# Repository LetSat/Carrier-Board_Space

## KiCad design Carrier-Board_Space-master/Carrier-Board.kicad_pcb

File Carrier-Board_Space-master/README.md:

# Carrier-Board_Space
mCom-TK1 carrier board. This is the actual board for space.

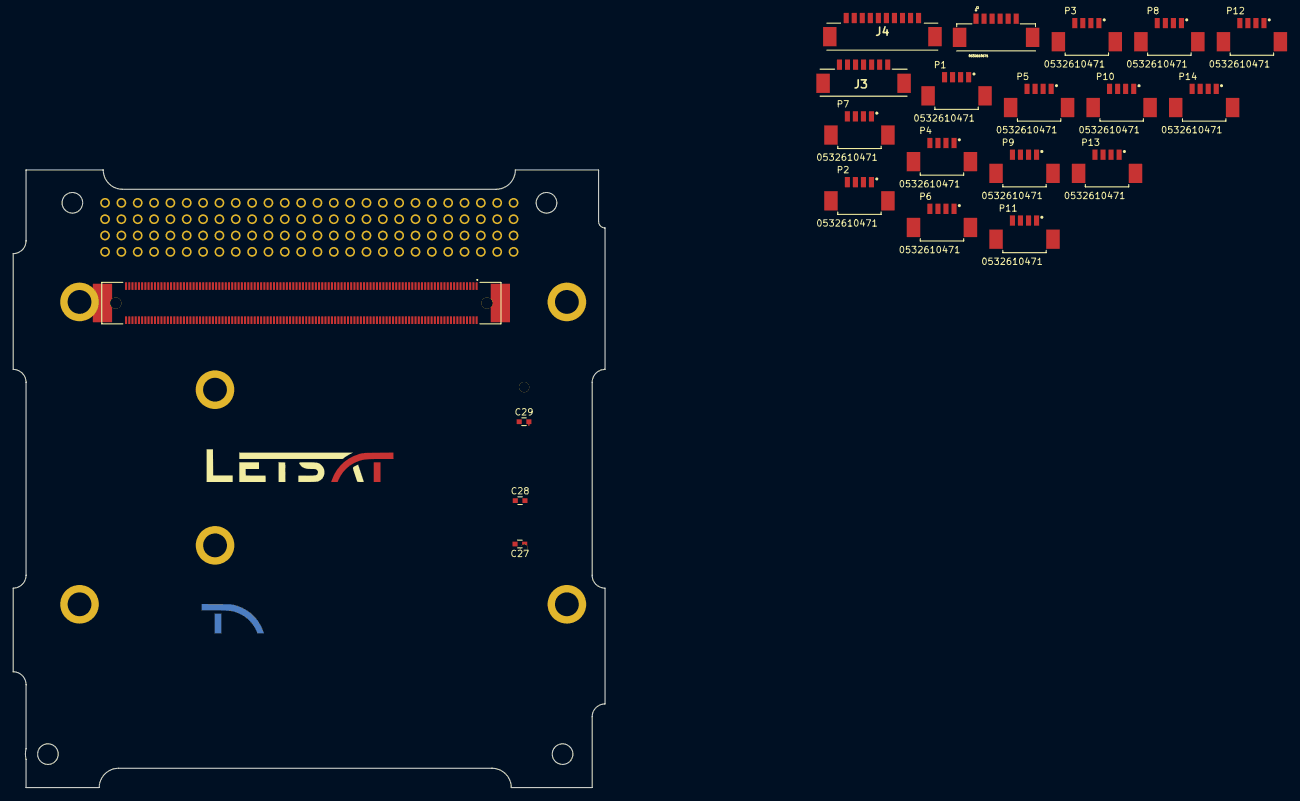
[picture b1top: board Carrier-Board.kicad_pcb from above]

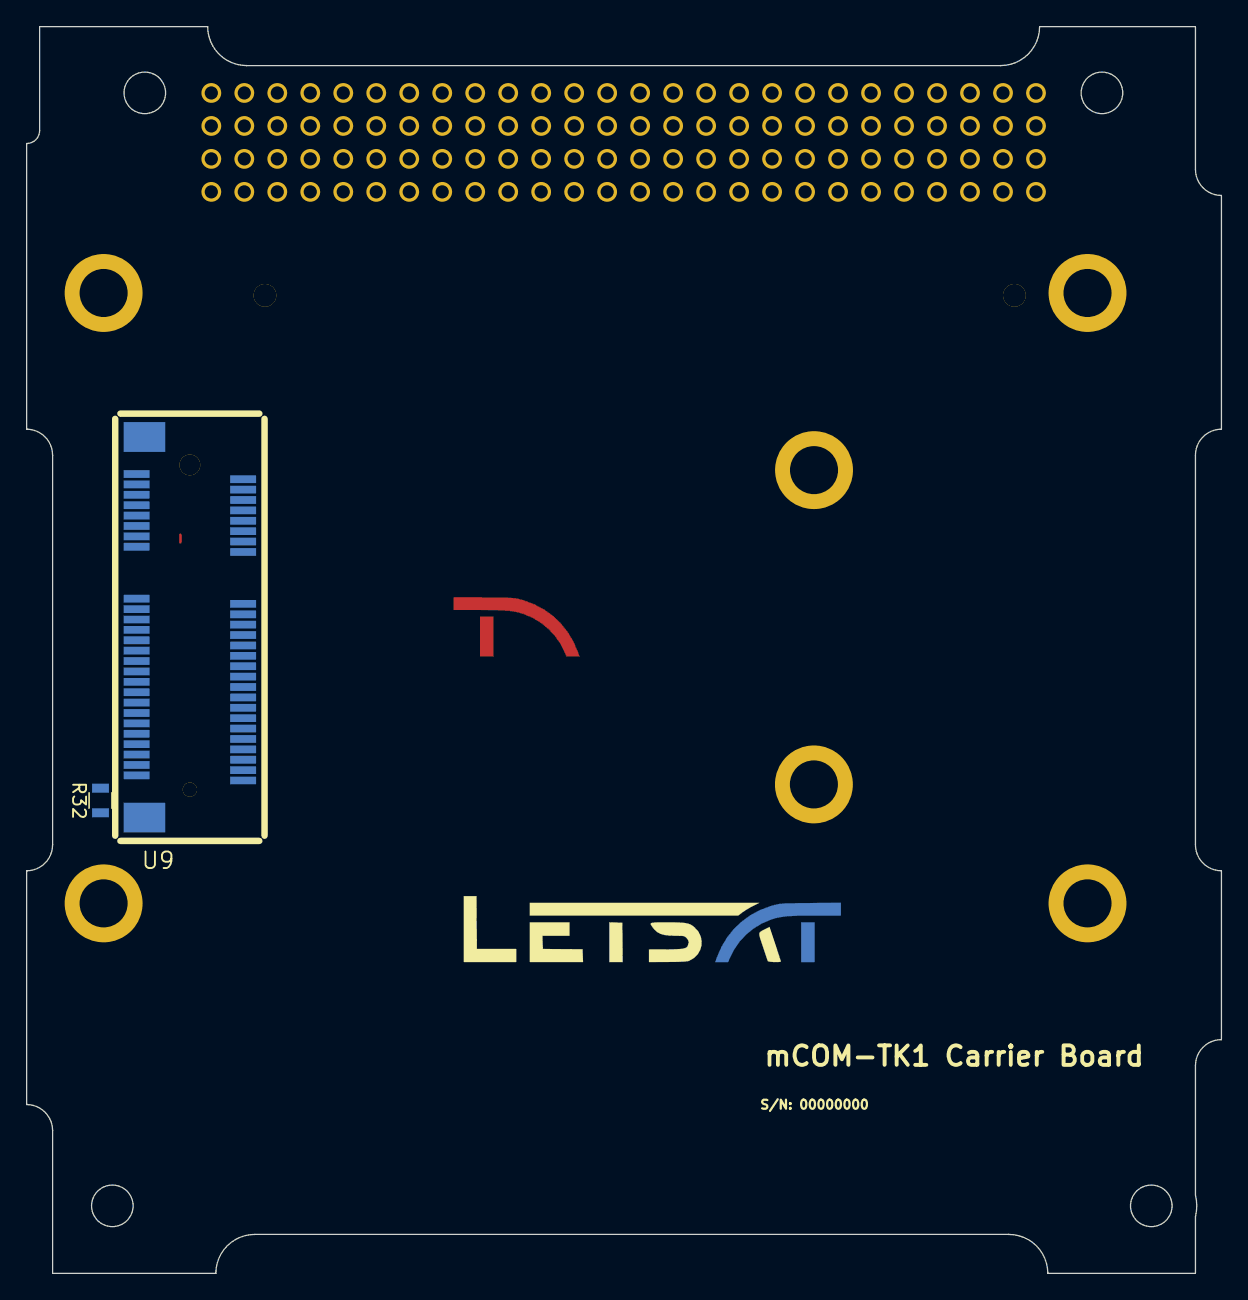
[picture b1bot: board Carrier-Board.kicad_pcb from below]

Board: 4 copper layers, 92.0 x 96.0 mm, 27 parts (4 on the bottom side), 20 nets.

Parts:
C27, C28, C29: .1uF; C_0603
G1, G1#2: LOGO; LetSatLogo440
H1: H1; ESQ-126-XX-X-D
H2: H2; ESQ-126-XX-X-D
J1: CONN_3-6318491-6; MCOM10-K1
J2: 0532610671; MOLEX_0532610671
J3: 53261-0771
J4: 53261-1071; 532611071
P1, P2, P3, P4, P5, P6, P7, P8, P9, P10, P11, P12, P13, P14: 0532610471; MOLEX_0532610471
R32: 0; R_0805
U9: MSATA-Socket; mpcie-socket

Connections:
3V3: H2.27, H2.28
5V: H2.25, H2.26
12V: H2.23, H2.24
+3.3V: C27.1, C28.1, C29.1, U9.2, U9.24, U9.39, U9.41, U9.52
BCR_OUT: H2.41, H2.42, H2.43, H2.44
BatV: H2.45, H2.46
DNU: H2.33, H2.34, H2.37, H2.38, H2.39, H2.40
GND: H2.9, H2.14, H2.17, H2.21, H2.22, H2.29, H2.30, H2.32, H2.47, H2.48
GNDREF: C27.2, C28.2, C29.2, R32.2, U9.4, U9.9, U9.15, U9.18, U9.21, U9.26, U9.27, U9.29, U9.34, U9.35, U9.37, U9.40, U9.50
unnamed: J2.S1, J2.S2
unnamed: R32.1, U9.51
PCM_IN: H2.35, H2.36
SATA0_RX+: J1.19, U9.23
SATA0_RX-: J1.20, U9.25
SATA0_TX+: J1.16, U9.33
SATA0_TX-: J1.17, U9.31
SATA_ACTn: J1.28, U9.49
mCOM_5V_SBY: J1.194, J1.195, J1.196, J1.197
mCOM_12V: J1.104, J1.105, J1.106, J1.107, J1.108, J1.109, J1.214, J1.215, J1.216, J1.217, J1.218, J1.219
mCOM_GND: J1.1, J1.11, J1.21, J1.31, J1.41, J1.51, J1.57, J1.60, J1.66, J1.70, J1.80, J1.90, J1.100, J1.110, J1.111, J1.121, J1.131, J1.141, J1.151, J1.161, J1.170, J1.180, J1.190, J1.200, J1.210, J1.220

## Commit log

2018-02-03 Proto Carrier mirror
2018-02-03 asdf
2018-02-03 removed stuff we dont need
2018-03-27 stuff
2018-03-27 Update mCOM connector, correct header refs/silk
2018-03-28 added connecttos in lib
2018-03-28 ADSFM
2018-04-19 Populated MCOM Connectors
